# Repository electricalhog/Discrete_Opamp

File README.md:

# Discrete Opamp
## Designed using off-the-shelf components

https://github.com/user-attachments/assets/8ae4dc66-9749-4e35-9709-75ff86e5063c

Real-world testing demonstrated its basic functionality but fell short of optimistic simulation data.

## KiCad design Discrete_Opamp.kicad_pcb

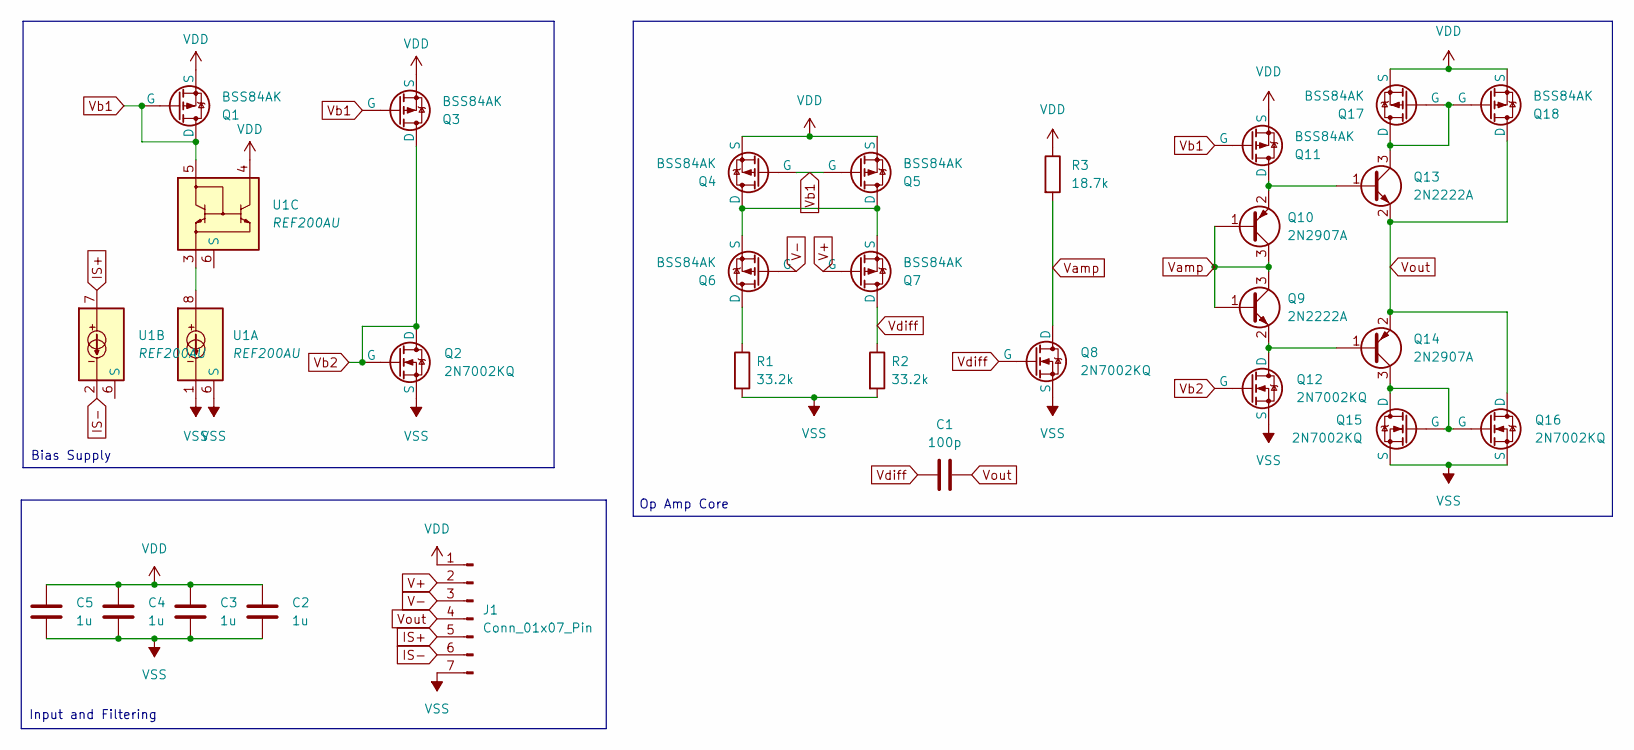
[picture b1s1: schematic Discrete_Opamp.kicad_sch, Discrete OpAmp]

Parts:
C1: 100p; C_0603_1608Metric
C2, C3, C4, C5: 1u; C_0603_1608Metric
J1: Conn_01x07_Pin; PinHeader_1x07_P2.54mm_Vertical
Q1, Q3, Q4, Q5, Q6, Q7, Q11, Q17, Q18: BSS84AK; SOT8015
Q2, Q8, Q12, Q15, Q16: 2N7002KQ; SOT8015
Q9, Q13: 2N2222A; SOT-883
Q10, Q14: 2N2907A; SOT-883
R1, R2: 33.2k; R_0603_1608Metric
R3: 18.7k; R_0603_1608Metric
U1: REF200AU; SOIC-8_3.9x4.9mm_P1.27mm

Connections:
IS+: J1.5, U1.7
IS-: J1.6, U1.2
unnamed: Q4.3 (D), Q5.3 (D), Q6.2 (S), Q7.2 (S)
unnamed: Q6.3 (D), R1.1
unnamed: Q10.2 (E), Q11.3 (D), Q13.1 (B)
unnamed: Q9.2 (E), Q12.3 (D), Q14.1 (B)
unnamed: Q13.3 (C), Q17.1 (G), Q17.3 (D), Q18.1 (G)
unnamed: Q14.3 (C), Q15.1 (G), Q15.3 (D), Q16.1 (G)
unnamed: U1.3, U1.8
V+: J1.2, Q7.1 (G)
V-: J1.3, Q6.1 (G)
VDD: C2.2, C3.2, C4.2, C5.2, J1.1, Q1.2 (S), Q3.2 (S), Q4.2 (S), Q5.2 (S), Q11.2 (S), Q17.2 (S), Q18.2 (S), R3.1, U1.4
VSS: C2.1, C3.1, C4.1, C5.1, J1.7, Q2.2 (S), Q8.2 (S), Q12.2 (S), Q15.2 (S), Q16.2 (S), R1.2, R2.2, U1.1, U1.6 (S)
Vamp: Q8.3 (D), Q9.1 (B), Q9.3 (C), Q10.1 (B), Q10.3 (C), R3.2
Vb1: Q1.1 (G), Q1.3 (D), Q3.1 (G), Q4.1 (G), Q5.1 (G), Q11.1 (G), U1.5
Vb2: Q2.1 (G), Q2.3 (D), Q3.3 (D), Q12.1 (G)
Vdiff: C1.1, Q7.3 (D), Q8.1 (G), R2.1
Vout: C1.2, J1.4, Q13.2 (E), Q14.2 (E), Q16.3 (D), Q18.3 (D)

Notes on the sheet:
Bias Supply
Op Amp Core
Input and Filtering

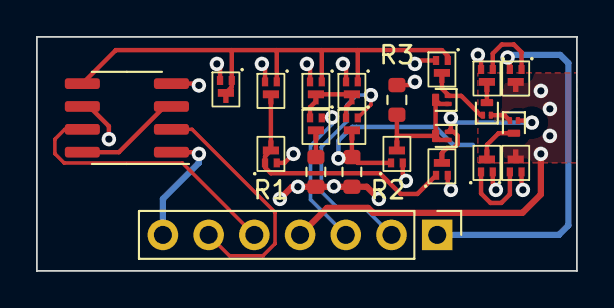
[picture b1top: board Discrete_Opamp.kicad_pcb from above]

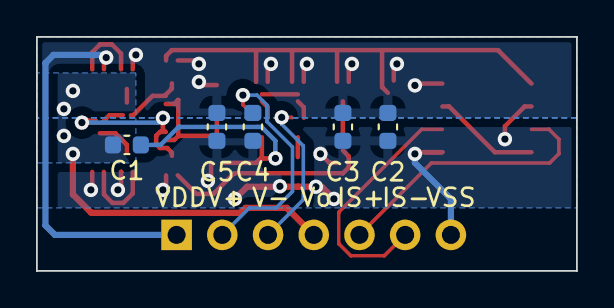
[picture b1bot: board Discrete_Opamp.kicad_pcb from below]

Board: 2 copper layers, 30.0 x 13.0 mm, 28 parts (5 on the bottom side), 18 nets.

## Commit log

2024-08-08 init
2024-08-08 added design files
2024-08-08 file orginization
2024-08-08 added media files
2024-08-08 Create README.md
    Testing embedded .mov feature
2024-08-08 rescale video
2024-08-08 10MB limit
